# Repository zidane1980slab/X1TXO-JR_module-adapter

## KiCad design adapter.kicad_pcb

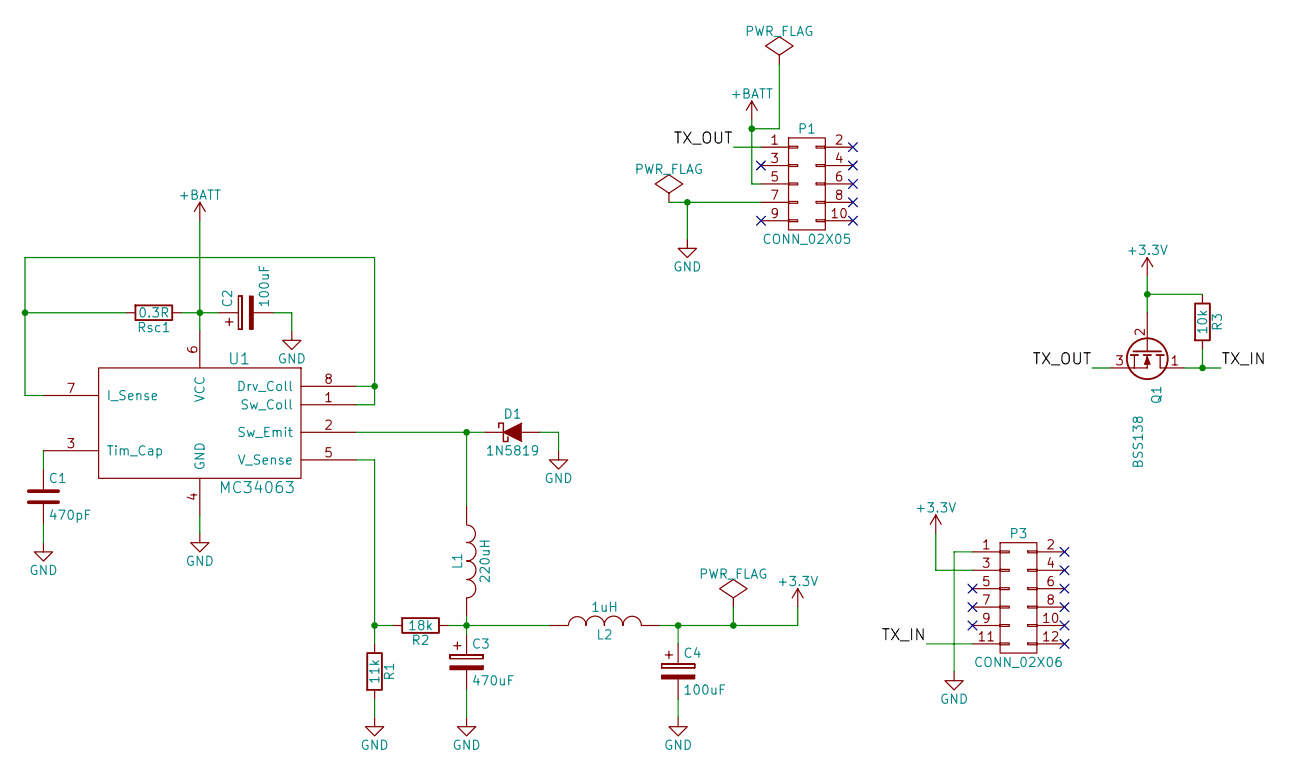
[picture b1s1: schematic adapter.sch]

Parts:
C1: 470pF; C_0805_HandSoldering
C2: 100uF; c_elec_6.3x7.7
C3: 470uF; c_elec_10x10.5
C4: 100uF; c_elec_6.3x5.7
D1: 1N5819; Diode-MELF_Handsoldering
L1: 220uH; SMT73
L2: 1uH; Choke_SMD_1206_Handsoldering
P1: CONN_02X05; Socket_Strip_Straight_2x05
P3: CONN_02X06; Socket_Strip_Straight_2x06_pitch2mm
Q1: BSS138; SOT-23_Handsoldering
R1: 11k; R_0805_HandSoldering
R2: 18k; R_0805_HandSoldering
R3: 10k; R_0805_HandSoldering
Rsc1: 0.3R; Resistor_Horizontal_RM10mm
U1: MC34063; SOIC-8_3.9x4.9mm_Pitch1.27mm

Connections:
+3V3: C4.1, L2.2, P3.3, Q1.2 (G), R3.1; also elsewhere on the board
+BATT: C2.1, P1.5, Rsc1.1, U1.6 (VCC)
/TX_IN: P3.11, Q1.1 (D), R3.2; also elsewhere on the board
/TX_OUT: P1.1, Q1.3 (S)
GND: C1.2, C2.2, C3.2, C4.2, D1.2 (A), P1.7, P3.1, R1.2, U1.4 (GND); also elsewhere on the board
unnamed: C1.1, U1.3 (Tim_Cap)
unnamed: C3.1, L1.2, L2.1, R2.1
unnamed: D1.1 (K), L1.1, U1.2 (Sw_Emit)
unnamed: R1.1, R2.2, U1.5 (V_Sense)
unnamed: Rsc1.2, U1.1 (Sw_Coll), U1.7 (I_Sense), U1.8 (Drv_Coll)

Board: 2 copper layers, 15 parts (12 on the bottom side), 10 nets, no tracks yet.

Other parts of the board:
P2: CONN_02X06; Socket_Strip_Straight_2x06_pitch2mm

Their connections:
+3V3: P2.3; also elsewhere on the board
/TX_IN: P2.11; also elsewhere on the board
GND: P2.1; also elsewhere on the board

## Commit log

2015-07-25 init
2015-07-26 Changed 2mm pitch array footpring a little.
2015-07-26 Almost finished.
